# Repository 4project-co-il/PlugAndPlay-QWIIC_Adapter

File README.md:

# PlugAndPlay: QWIIC Adapter
This is the repository with the files for PlugAndPlay adapter for QWIIC/STEMA QT devices.

That module allows connecting QWIIC/STEMA QT devices to the Plug-n-Play system with the JST-SH 4/6pin cables and includes also a 2pin female header that allows connection of the 2 interrupt lines that is used by the Plug-n-Play system.
The 2 interrupt lines are available as 2 solder holes as well, for those who are interested in a more permanent connection.

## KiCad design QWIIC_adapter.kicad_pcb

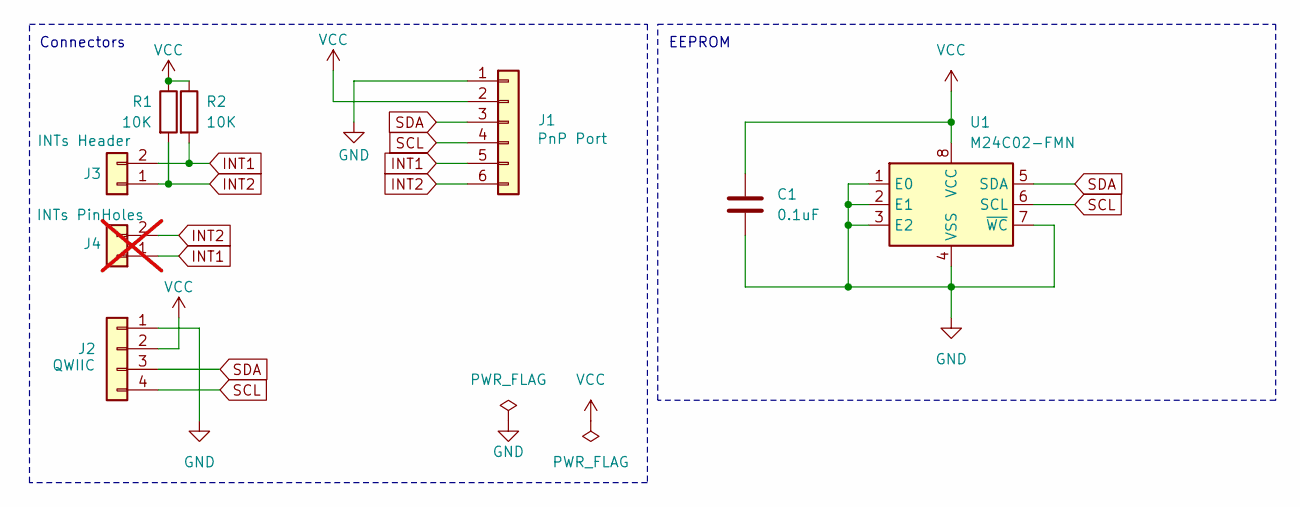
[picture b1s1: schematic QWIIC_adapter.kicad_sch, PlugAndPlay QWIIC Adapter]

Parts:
C1: 0.1uF; C_0603_1608Metric; MPN C14663
J1: JST_SH_SM06B-SRSS-TB_1x06-1MP_P1.00mm_Horizontal; MPN C7430448
J2: JST_SH_SM04B-SRSS-TB_1x04-1MP_P1.00mm_Horizontal; MPN C7430446
J3: PinHeader_1x02_P2.54mm_Horizontal_SMD; MPN C5142235
J4: Conn_01x02; PinSocket_1x02_P2.54mm_Vertical; not fitted
R1, R2: 10K; R_0603_1608Metric; MPN C25804
U1: M24C02-FMN; SOIC-8_3.9x4.9mm_P1.27mm; MPN C114502

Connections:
GND: C1.2, J1.1, J2.1, U1.1 (E0), U1.2 (E1), U1.3 (E2), U1.4 (VSS), U1.7 (~WC)
INT1: J1.5, J3.2, J4.1, R2.2
INT2: J1.6, J3.1, J4.2, R1.2
SCL: J1.4, J2.4, U1.6 (SCL)
SDA: J1.3, J2.3, U1.5 (SDA)
VCC: C1.1, J1.2, J2.2, R1.1, R2.1, U1.8 (VCC)

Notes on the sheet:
EEPROM
Connectors

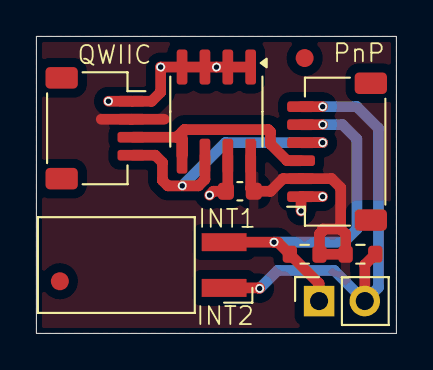
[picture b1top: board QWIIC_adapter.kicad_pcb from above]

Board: 2 copper layers, 20.0 x 16.5 mm, 8 parts (0 on the bottom side), 6 nets.

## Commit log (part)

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2025-05-19 Panel framing on all 4 sides
